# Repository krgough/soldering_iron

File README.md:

# soldering_iron

Schematic, PCB and Firmware for a temperature controlled soldering iron.   
Based on >> https://www.instructables.com/DIY-Digital-Soldering-Station/?utm_source=newsletter&utm_medium=email

## Design Notes
Soldering Iron has a 5 ohm heater coil and a PTC temperature sensor.  So we switch our source voltage (24v or less) via  a mosfet through the heater to operate the iron.  We measure the tip temperature via the PTC.

Wanted Temp Range = 500-24'C = 475 degree steps
10 bit ADC resolution = 5 v* (2^10 - 1) = 4.887mV/div

PTC Values are approx:
24'C = 50R
500'C = 215R

For the PTC we use a potential divider of 470R + PTC(approx 50R at 24'C).   This results in a voltage range of around 0.48v - 1.49v = 1v = 207 ADC steps.   Each ADC step is therefore equivalent to more than 1'C, so we would have missing temperature values.

To overcome that problem we use an opamp with a gain of 2.22
G = Rf/Ri + 1 = 3300/2700 + 1 = 2.22

24'C    = 0.48 * 2.22 = 1.06v
500'C = 1.57 * 2.22 = 3.49v

This gives a range of 2.25v or 497 ADC steps.

Note that Max Vout from LM358 is around 3v5 when running from 5v, so it's hard to get any more without introducing a level shift as well.  I did experiment with using the spare opamp as a unity gain buffer to put a non-zero voltage on the gain setting resistor that would normally be connected to ground - this seemed to create odd behaviour (output was not linear) so I abandoned that as the simple solution above seems to be close enough.

## Display
We use a 16x2 LCD with a I2C interface.  In my case I'm using an Adafruit module that was originally purchased for use with an rPi.

## Spare OpAmp
Terminated the device as a unity gain buffer with input set to mid rail.

## Adjustable SMPS
We power the device with 18-24v and then use the SMPS to regulate down to 5v for the control circuits and display.  Since the SMPS is adjustable I put a jumper in the output so that I can adjust the voltage with the rest of the circuit disconnected.

## Firmware
- We average the readings to try to reduce any noise for the control loop.
- Display refresh - we limit the refresh rate to once a second to stop and annoying flickering 
- Hysteresis - We have implemented some temperature hysteresis on the control loop to prevent rapid switching - it may not be required but it seems to be sensible to prevent any rapid oscillations.

## Protection/Safety Considerations (To be done - not yet implemented)
The Iron can reach 500'C or higher when left on continuously.  For safety I think it's worth having a couple of features...
- If the Arduino crashes with the MOSFET on then Iron can overheat.  Mitigation is to implement watchdog in Arduino so that a WD Reset will occur if the device locks out for some reason.  This is not entirely ideal - We could also have some external circuit like a monostable, so that we have to keep sending pulses to the monostable to enable the MOSFET, but this would require additional circuitry.
- Limit the max use time to x minutes.  Use a timer to turn the Iron to standby after a given time.  User needs to adjust the setpoint to make it come back on.  Iron shall start up in standby so that user interaction is required before the heater is turned on.   Suggest this is done by creating a new state variable "bool standby = 0".   Standby is disabled by a change of > 5'C on the setpoint.

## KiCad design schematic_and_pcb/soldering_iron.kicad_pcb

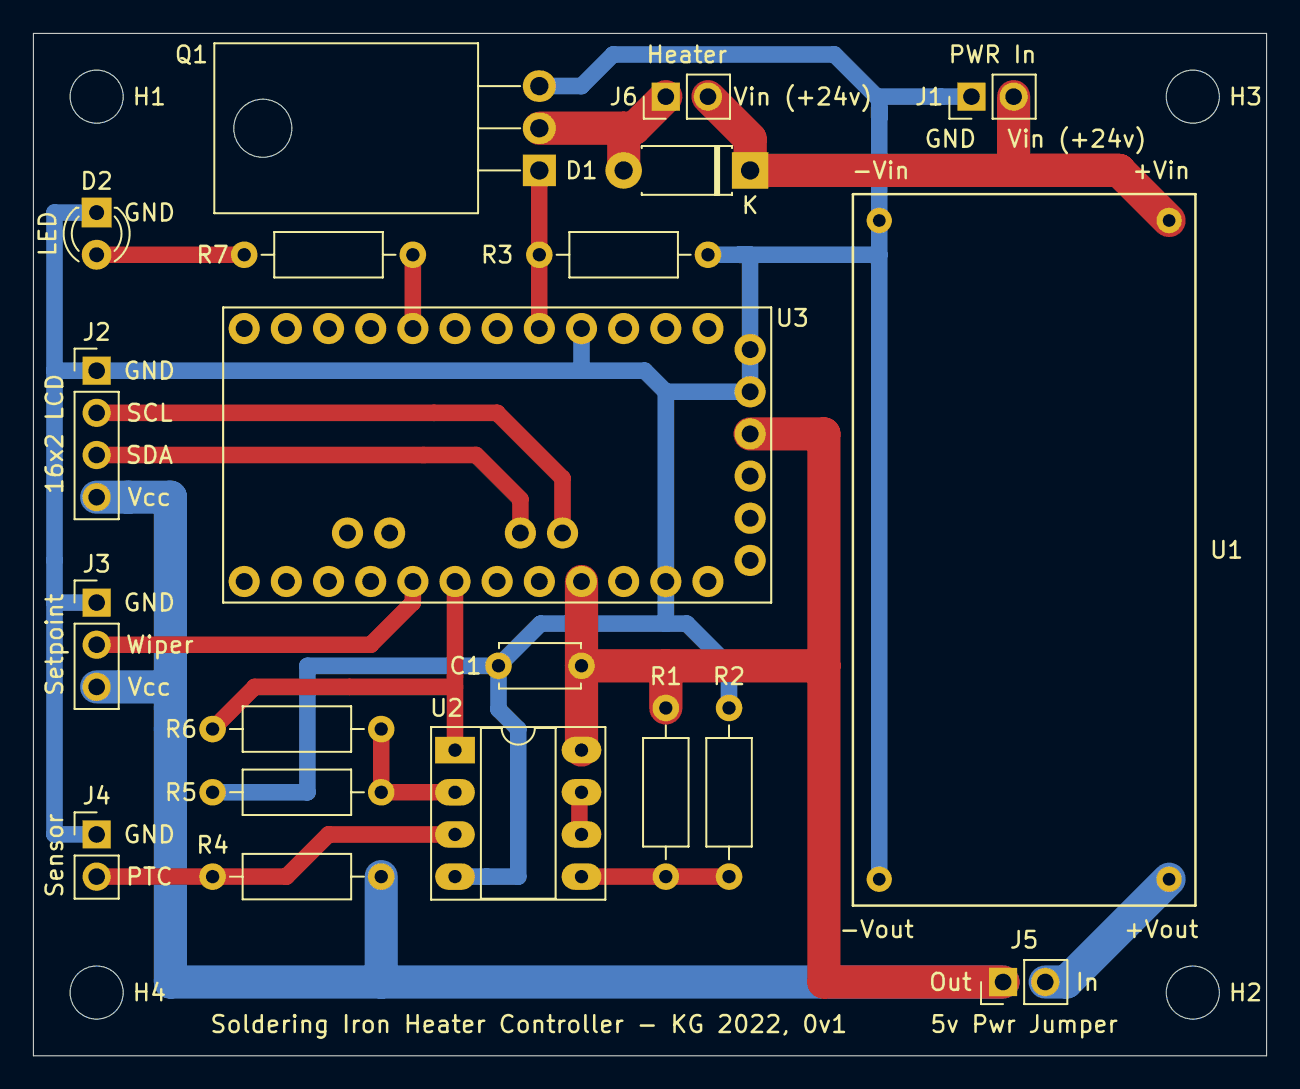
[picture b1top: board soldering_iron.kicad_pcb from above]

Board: 2 copper layers, 74.3 x 61.6 mm, 24 parts (0 on the bottom side), 16 nets.

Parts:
C1: 100n; C_Disc_D4.7mm_W2.5mm_P5.00mm
D1: 1N4004; D_DO-41_SOD81_P7.62mm_Horizontal
D2: LED; LED_D3.0mm
H1, H2, H3, H4: MountingHole; MountingHole_3.2mm_M3
J1: PWR In; PinHeader_1x02_P2.54mm_Vertical
J2: 16x2 LCD; PinHeader_1x04_P2.54mm_Vertical
J3: Setpoint; PinHeader_1x03_P2.54mm_Vertical
J4: Sensor; PinHeader_1x02_P2.54mm_Vertical
J5: 5v Pwr Jumper; PinHeader_1x02_P2.54mm_Vertical
J6: Heater; PinHeader_1x02_P2.54mm_Vertical
Q1: IRLZ44N; TO-220-3_Horizontal_TabDown
R1, R2, R3: 10k; R_Axial_DIN0207_L6.3mm_D2.5mm_P10.16mm_Horizontal
R4: 470R; R_Axial_DIN0207_L6.3mm_D2.5mm_P10.16mm_Horizontal
R5: 2k7; R_Axial_DIN0207_L6.3mm_D2.5mm_P10.16mm_Horizontal
R6: 3k3; R_Axial_DIN0207_L6.3mm_D2.5mm_P10.16mm_Horizontal
R7: 1k; R_Axial_DIN0207_L6.3mm_D2.5mm_P10.16mm_Horizontal
U1: SMPS_24v_5v
U2: LM358; DIP-8_W7.62mm_Socket_LongPads
U3: ARDUINO_PRO_MINI; MODULE_ARDUINO_PRO_MINI

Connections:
+24v: D1.1, J1.2, J6.2, U1.4
GND: C1.2, D2.1, J1.1, J2.1, J3.1, J4.1, Q1.3, R2.2, R3.2, R5.2, U1.1, U1.2, U2.4, U3.JP1_5, U3.JP1_6, U3.JP6_2, U3.JP7_9
HEAT: Q1.1, R3.1, U3.JP7_8
unnamed: D1.2, J6.1, Q1.2
unnamed: D2.2, R7.1
unnamed: J5.2, U1.3
unnamed: R1.2, R2.1, U2.5
unnamed: R5.1, R6.2, U2.2
unnamed: R7.2, U3.JP7_5
unnamed: U2.6, U2.7
PTC: J4.2, R4.2, U2.3
PTC_SENSOR: R6.1, U2.1, U3.JP6_7
SCL: J2.2, U3.JP2_2
SDA: J2.3, U3.JP2_1
SETPOINT: J3.2, U3.JP6_8
VCC: C1.1, J2.4, J3.3, J5.1, R1.1, R4.1, U2.8, U3.JP1_4, U3.JP6_4
